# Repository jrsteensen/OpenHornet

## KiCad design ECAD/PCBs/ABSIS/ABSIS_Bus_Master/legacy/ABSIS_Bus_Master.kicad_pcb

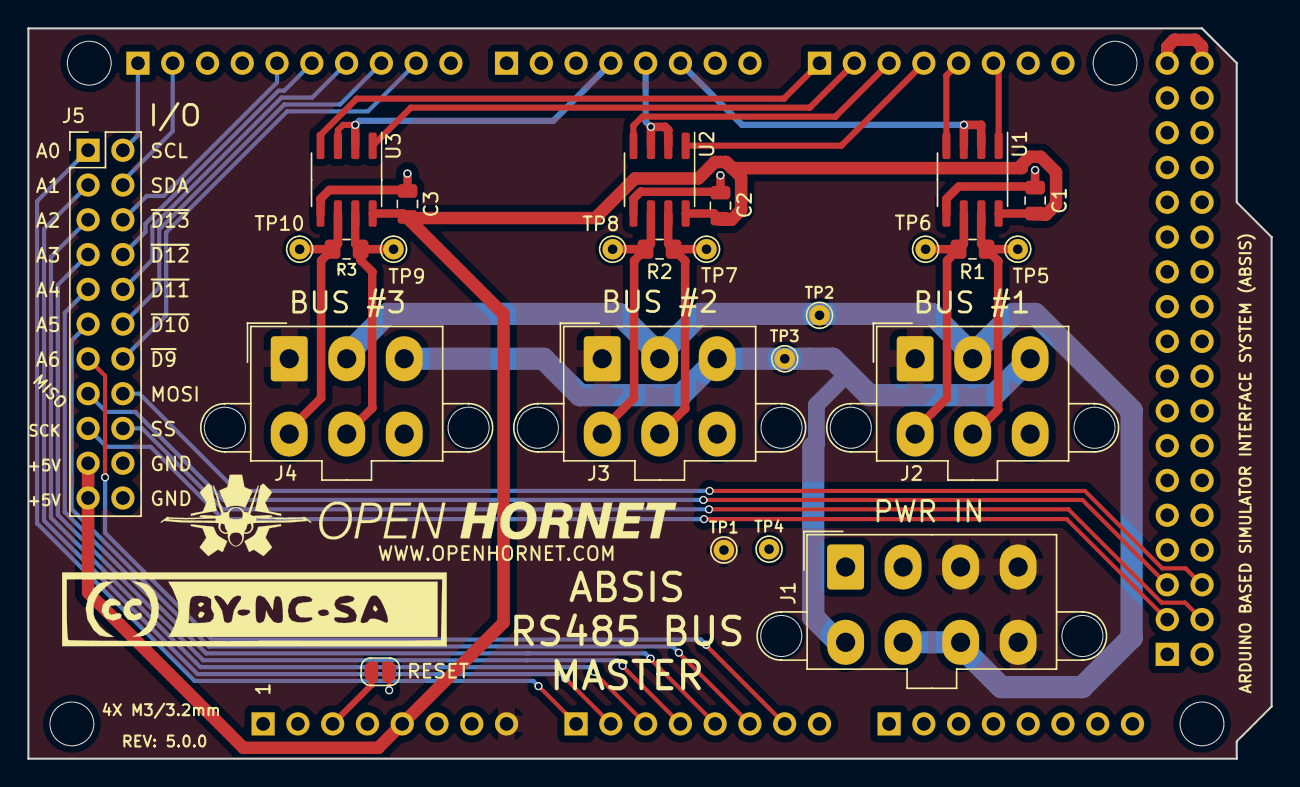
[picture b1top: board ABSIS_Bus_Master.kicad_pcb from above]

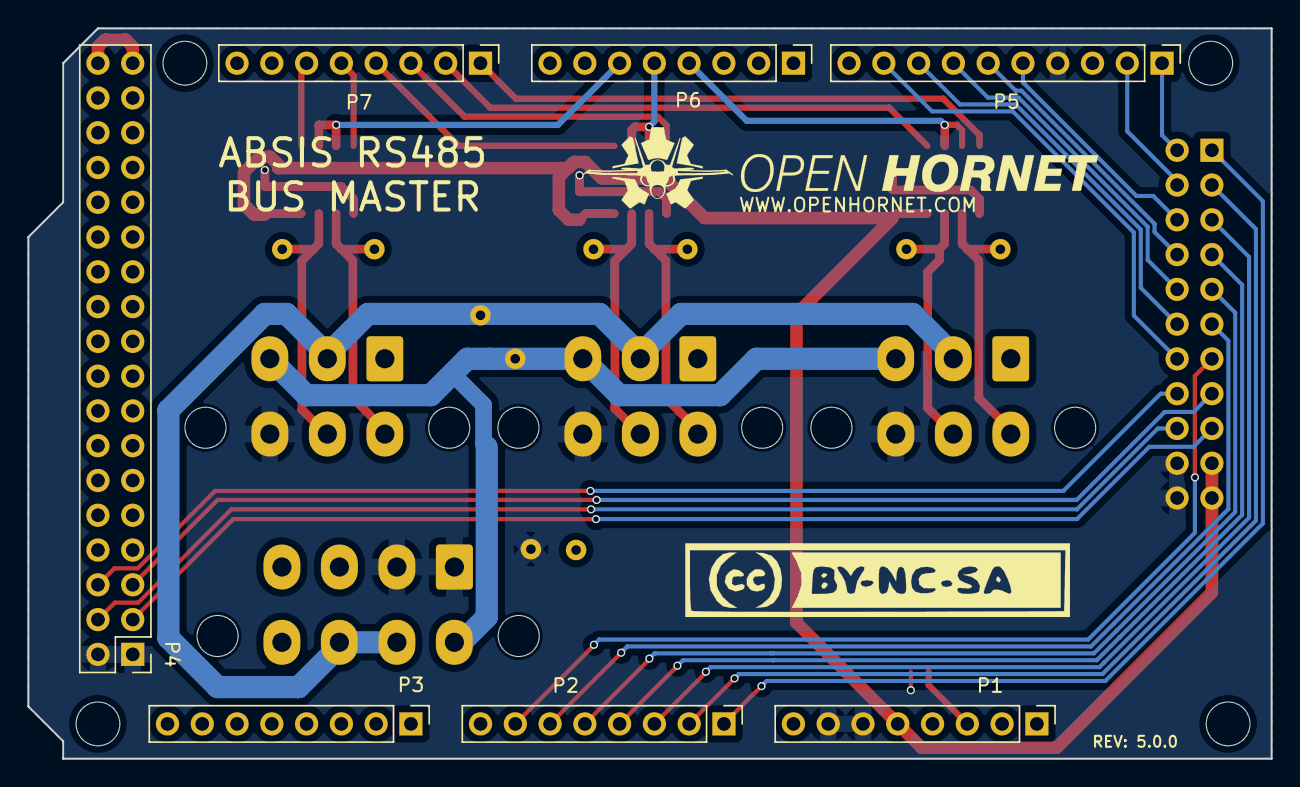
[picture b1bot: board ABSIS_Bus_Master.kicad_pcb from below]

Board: 2 copper layers, 90.8 x 53.3 mm, 40 parts (9 on the bottom side), 40 nets.

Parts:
C1, C2, C3: 0.1uF; C_0805_2012Metric
J1: Mini-Fit Jr. 2x04; Molex_Mini-Fit_Jr_5566-08A2_2x04_P4.20mm_Vertical
J2, J3, J4: Mini-Fit Jr. 2x03; Molex_Mini-Fit_Jr_5566-06A2_2x03_P4.20mm_Vertical
J5: PinHeader_2x11; PinHeader_2x11_P2.54mm_Vertical
LOGO1, LOGO4: LOGO; LOGO_CC-BY-NC-SA_Half_Large
LOGO2, LOGO3: LOGO; LOGO_OH_Text_Small
MK1, MK3, MK4, MK6: MH; MountingHole_3.2mm_M3_DIN965
P1: Power; PinHeader_1x08_P2.54mm_Vertical
P2, P3: Analog; PinHeader_1x08_P2.54mm_Vertical
P4: Digital; PinHeader_2x18_P2.54mm_Vertical
P5: PWM; PinHeader_1x10_P2.54mm_Vertical
P6: PWM; PinHeader_1x08_P2.54mm_Vertical
P7: Communication; PinHeader_1x08_P2.54mm_Vertical
R1, R2, R3: 120; R_0805_2012Metric_Pad1.15x1.40mm_HandSolder
RST1: RST; SolderJumper-2_P1.3mm_Open_RoundedPad1.0x1.5mm
TP1: TP-12; TestPoint_THTPad_D1.5mm_Drill0.7mm
TP2: TP-5V; TestPoint_THTPad_D1.5mm_Drill0.7mm
TP3: TP-3.3V; TestPoint_THTPad_D1.5mm_Drill0.7mm
TP4: TP-GND; TestPoint_THTPad_D1.5mm_Drill0.7mm
TP5: TP-B1B; TestPoint_THTPad_D1.5mm_Drill0.7mm
TP6: TP-B1A; TestPoint_THTPad_D1.5mm_Drill0.7mm
TP7: TP-B2B; TestPoint_THTPad_D1.5mm_Drill0.7mm
TP8: TP-B2A; TestPoint_THTPad_D1.5mm_Drill0.7mm
TP9: TP-B3B; TestPoint_THTPad_D1.5mm_Drill0.7mm
TP10: TP-B3A; TestPoint_THTPad_D1.5mm_Drill0.7mm
U1, U2, U3: MAX487EESA+T; SOIC-8_3.9x4.9mm_P1.27mm

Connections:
+5V: C1.1, C2.1, C3.1, J5.19, J5.21, P1.5, U1.8 (VCC), U2.8 (VCC), U3.8 (VCC)
+5VD: P4.35, P4.36
/2(**): P6.6, U1.2 (~RE), U1.3 (DE)
/3(**): P6.5, U2.2 (~RE), U2.3 (DE)
/4(**): P6.4, U3.2 (~RE), U3.3 (DE)
/9(**): J5.14, P5.9
/10(**): J5.12, P5.8
/11(**): J5.10, P5.7
/12(**): J5.8, P5.6
/13(**): J5.6, P5.5
/14(Tx3): P7.1, U3.4 (DI)
/15(Rx3): P7.2, U3.1 (RO)
/16(Tx2): P7.3, U2.4 (DI)
/17(Rx2): P7.4, U2.1 (RO)
/18(Tx1): P7.5, U1.4 (DI)
/19(Rx1): P7.6, U1.1 (RO)
/50(MISO): J5.15, P4.5
/51(MOSI): J5.16, P4.6
/52(SCK): J5.17, P4.3
/53(SS): J5.18, P4.4
/+3.3V_SUPPLY: J1.5, J2.3, J3.3, J4.3, TP3.1
/+5V_SUPPLY: J1.6, J1.7, J2.2, J3.2, J4.2, TP2.1
/+12V_SUPPLY: J1.3, J1.4, J1.8, J2.1, J3.1, J4.1, P1.8, TP1.1
/A0: J5.1, P2.1
/A1: J5.3, P2.2
/A2: J5.5, P2.3
/A3: J5.7, P2.4
/A4: J5.9, P2.5
/A5: J5.11, P2.6
/A6: J5.13, P2.7
/BUS1-A: J2.4, R1.2, TP6.1, U1.6 (A)
/BUS1-B: J2.5, R1.1, TP5.1, U1.7 (B)
/BUS2-A: J3.4, R2.2, TP8.1, U2.6 (A)
/BUS2-B: J3.5, R2.1, TP7.1, U2.7 (B)
/BUS3-A: J4.4, R3.2, TP10.1, U3.6 (A)
/BUS3-B: J4.5, R3.1, TP9.1, U3.7 (B)
/Reset: P1.3, RST1.2 (B)
/SCL: J5.2, P5.1
/SDA: J5.4, P5.2
GND: C1.2, C2.2, C3.2, J1.1, J1.2, J2.6, J3.6, J4.6, J5.20, J5.22, P1.6, P1.7, P4.1, P4.2, P5.4, RST1.1 (A), TP4.1, U1.5 (GND), U2.5 (GND), U3.5 (GND)

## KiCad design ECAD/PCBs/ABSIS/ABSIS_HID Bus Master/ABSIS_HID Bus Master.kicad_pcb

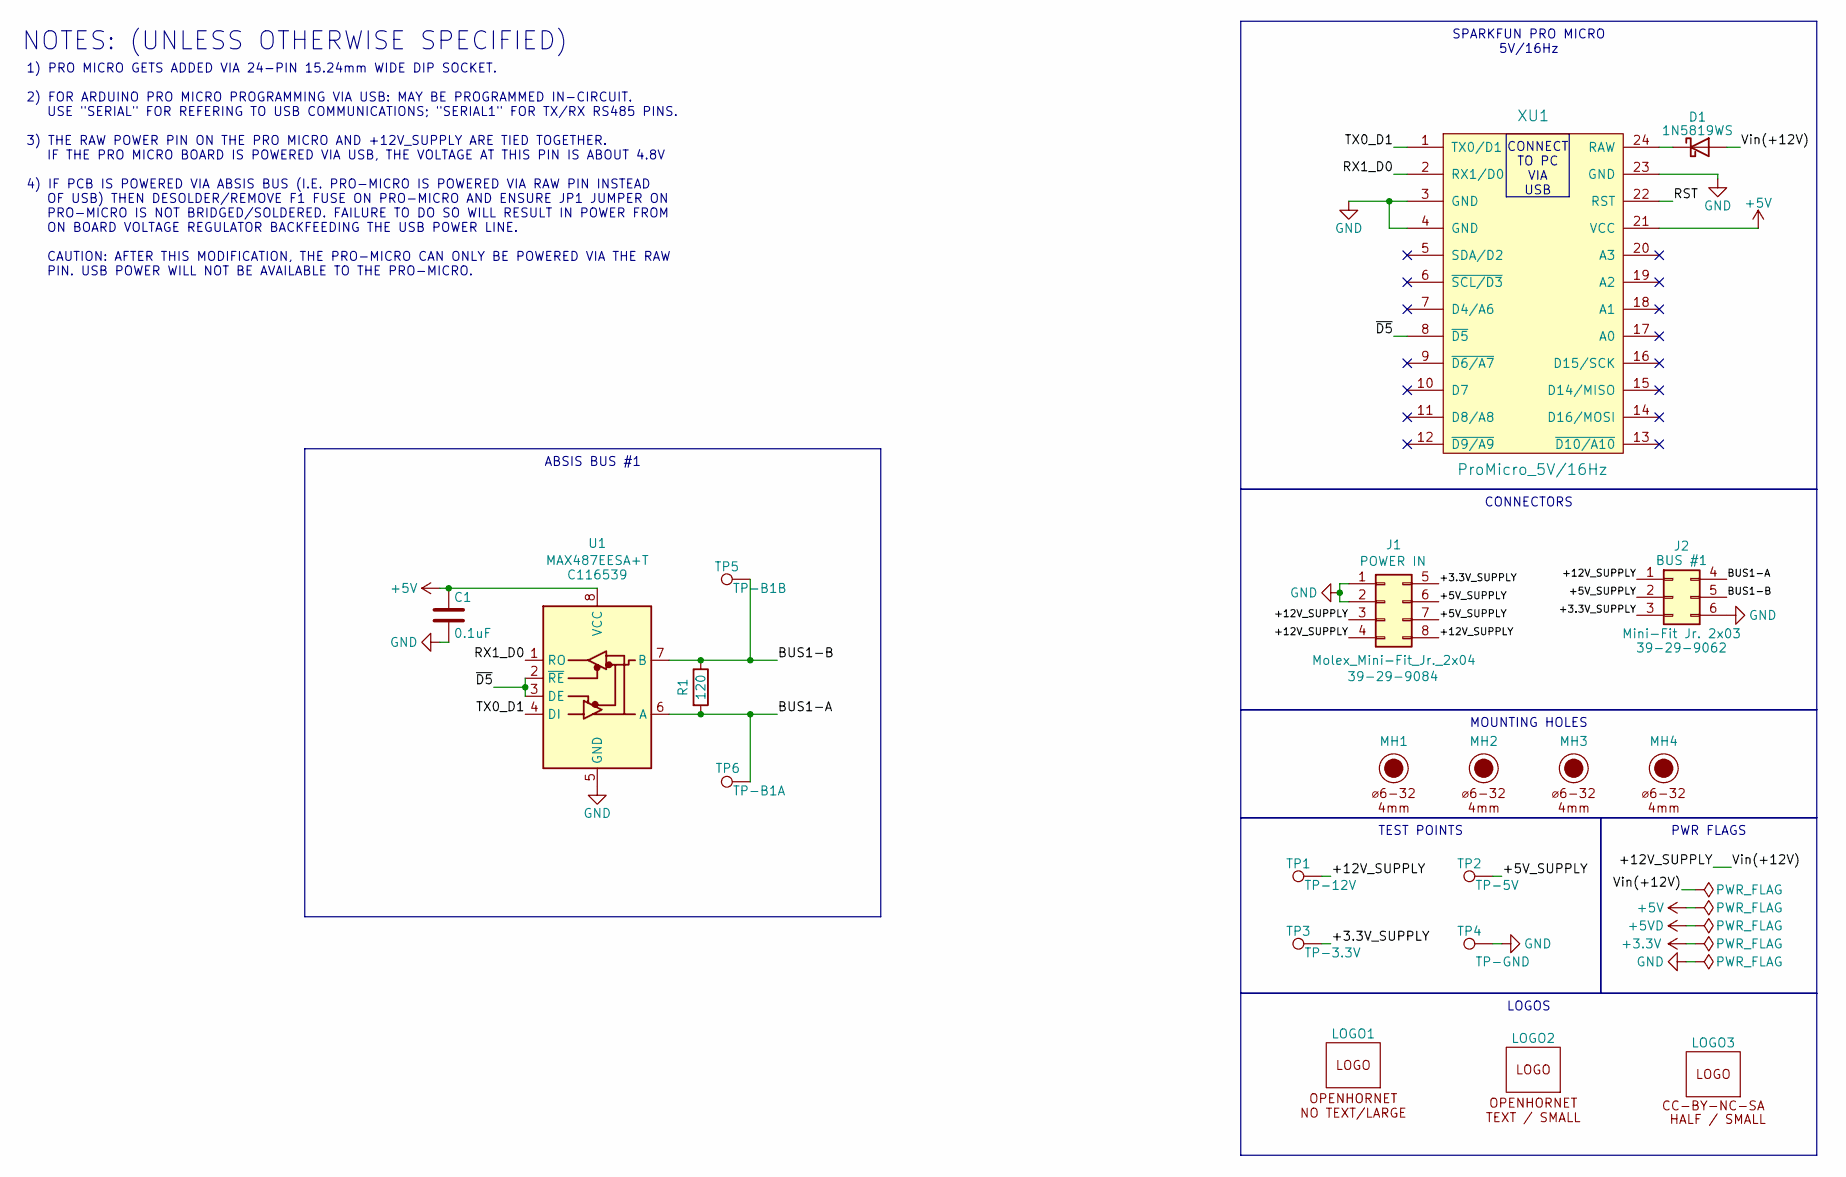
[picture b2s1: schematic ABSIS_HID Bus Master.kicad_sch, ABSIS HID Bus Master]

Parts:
C1: 0.1uF; C_0805_2012Metric; Manufacturer PN CC0805KRX7R9BB104; LCSC C49678
D1: 1N5819WS; D_SOD-323_HandSoldering; Manufacturer PN 1N5819WS; LCSC C191023
J1: Molex_Mini-Fit_Jr._2x04; Molex_Mini-Fit_Jr_5566-08A2_2x04_P4.20mm_Vertical; Manufacturer PN 39-29-9084; LCSC C587470
J2: Mini-Fit Jr. 2x03; Molex_Mini-Fit_Jr_5566-06A2_2x03_P4.20mm_Vertical; Manufacturer PN 39-29-9062; LCSC C505177
LOGO1: LOGO; LOGO_OH_NoText_Large
LOGO2: LOGO; LOGO_OH_Text_Small
LOGO3: LOGO; LOGO_CC-BY-NC-SA_Half_Small
MH1, MH2, MH3, MH4: 6x32 / 4mm; MountingHole_6-32_PHS
R1: 120; R_0805_2012Metric_Pad1.15x1.40mm_HandSolder; Manufacturer PN 0805W8F1200T5E; LCSC C17437
TP1, TP2, TP3, TP4, TP5, TP6: TestPoint; TestPoint_THTPad_D1.5mm_Drill0.7mm
U1: MAX487EESA+T; SOIC-8_3.9x4.9mm_P1.27mm; Manufacturer PN MAX487EESA+T; LCSC C116539
XU1: ProMicro_5V/16Hz; DIP-24_W15.24mm_Socket; Manufacturer PN Pro Micro - 5V/16MHz

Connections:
+5V: C1.1, U1.8 (VCC); also elsewhere on the board
/+3.3V_SUPPLY: J1.5, J2.3, TP3.1
/+5V_SUPPLY: J1.6, J1.7, J2.2, TP2.1
/+12V_SUPPLY: D1.2 (A), J1.3, J1.4, J1.8, J2.1, TP1.1
/BUS1-A: J2.4, R1.1, TP6.1, U1.6 (A)
/BUS1-B: J2.5, R1.2, TP5.1, U1.7 (B)
/RX1_D0: U1.1 (RO); also elsewhere on the board
/TX0_D1: U1.4 (DI); also elsewhere on the board
/~D5: U1.2 (~RE), U1.3 (DE); also elsewhere on the board
GND: C1.2, J1.1, J1.2, J2.6, TP4.1, U1.5 (GND); also elsewhere on the board
unnamed 11: D1.1 (K); also elsewhere on the board

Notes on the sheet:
CONNECTORS
SPARKFUN PRO MICRO 5V/16Hz
MOUNTING HOLES
PWR FLAGS
LOGOS
TEST POINTS
ABSIS BUS #1
CONNECT TO PC VIA USB
NOTES: (UNLESS OTHERWISE SPECIFIED)
1) PRO MICRO GETS ADDED VIA 24-PIN 15.24mm WIDE DIP SOCKET. 2) FOR ARDUINO PRO MICRO PROGRAMMING VIA USB: MAY BE PROGRAMMED IN-CIRCUIT. USE "SERIAL" FOR REFERING TO USB COMMUNICATIONS; "SERIAL1" FOR TX/RX RS485 PINS. 3) THE RAW POWER PIN ON THE PRO MICRO AND +12V_SUPPLY ARE TIED TOGETHER. IF THE PR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

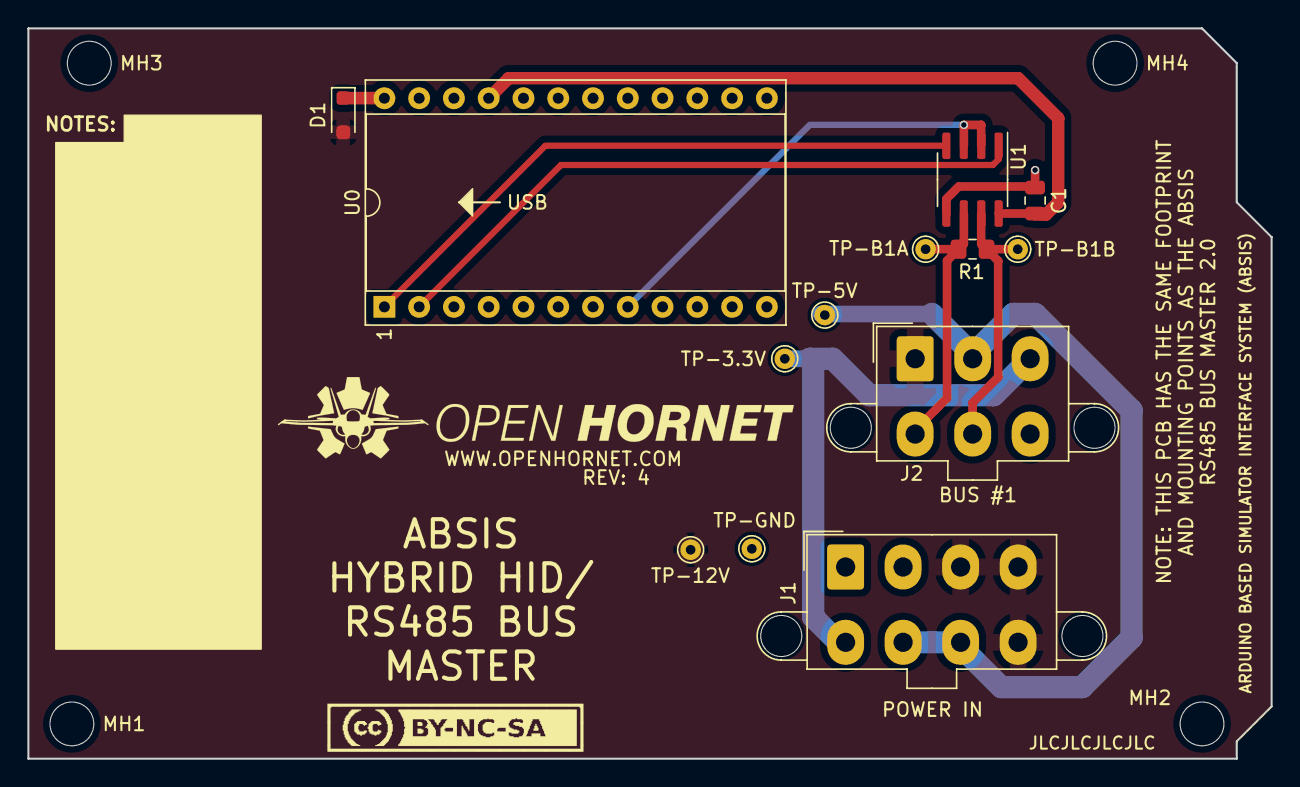
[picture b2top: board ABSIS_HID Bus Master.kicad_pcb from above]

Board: 2 copper layers, 90.8 x 53.3 mm, 20 parts (1 on the bottom side), 11 nets.

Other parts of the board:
U0: ProMicro_5V/16Hz; DIP-24_W15.24mm_Socket

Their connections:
+5V: U0.21 (VCC); also elsewhere on the board
/RX1_D0: U0.2 (RX1/D0); also elsewhere on the board
/TX0_D1: U0.1 (TX0/D1); also elsewhere on the board
/~D5: U0.8 (~D5); also elsewhere on the board
GND: U0.3 (GND), U0.4 (GND), U0.23 (GND); also elsewhere on the board
unnamed 11: U0.24 (RAW); also elsewhere on the board

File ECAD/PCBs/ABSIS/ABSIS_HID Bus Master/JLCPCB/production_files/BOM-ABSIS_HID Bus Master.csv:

Comment,Designator,Footprint,LCSC
MAX487EESA+T,U1,SOIC-8_3.9x4.9mm_P1.27mm,C116539
120,R1,R_0805_2012Metric_Pad1.15x1.40mm_HandSolder,C17437
0.1uF,C1,C_0805_2012Metric,C49678
Mini-Fit Jr. 2x03,J2,Molex_Mini-Fit_Jr_5566-06A2_2x03_P4.20mm_Vertical,C505177
Molex_Mini-Fit_Jr._2x04,J1,Molex_Mini-Fit_Jr_5566-08A2_2x04_P4.20mm_Vertical,C587470
ProMicro_5V/16Hz,U0,DIP-24_W15.24mm_Socket,

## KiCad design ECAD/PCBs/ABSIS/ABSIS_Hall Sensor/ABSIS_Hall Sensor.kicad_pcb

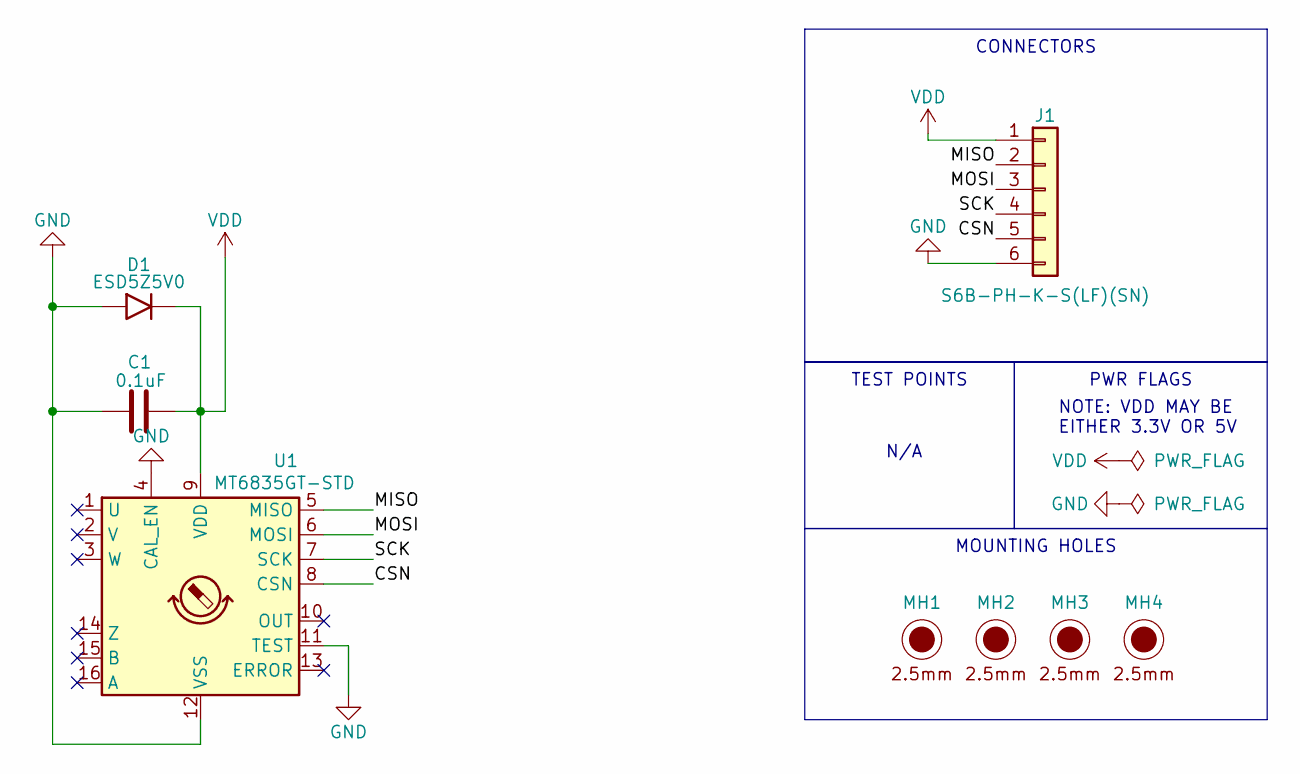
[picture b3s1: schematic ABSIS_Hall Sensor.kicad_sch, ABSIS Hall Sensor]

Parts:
C1: 0.1uF; C_0603_1608Metric; Manufacturer PN CC0603KRX7R9BB104; LCSC C14663
D1: ESD5Z5V0; D_SOD-523; Manufacturer PN ESD5Z5V0; LCSC C248788
J1: JST_PH_01x06; JST_PH_S6B-PH-K_1x06_P2.00mm_Horizontal; Manufacturer PN S6B-PH-K-S(LF)(SN); LCSC C265105
MH1, MH2, MH3, MH4: 2.5mm; MountingHole_2.5mm
U1: MT6835GT-STD; TSSOP-16_4.4x5mm_P0.65mm; Manufacturer PN MT6835GT-STD; LCSC C2932578

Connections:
/CSN: J1.5, U1.8 (CSN)
/MISO: J1.2, U1.5 (MISO)
/MOSI: J1.3, U1.6 (MOSI)
/SCK: J1.4, U1.7 (SCK)
GND: C1.2, D1.2 (A2), J1.6, U1.4 (CAL_EN), U1.11 (TEST), U1.12 (VSS)
VDD: C1.1, D1.1 (A1), J1.1, U1.9 (VDD)

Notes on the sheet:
MOUNTING HOLES
PWR FLAGS
CONNECTORS
TEST POINTS
N/A
NOTE: VDD MAY BE EITHER 3.3V OR 5V

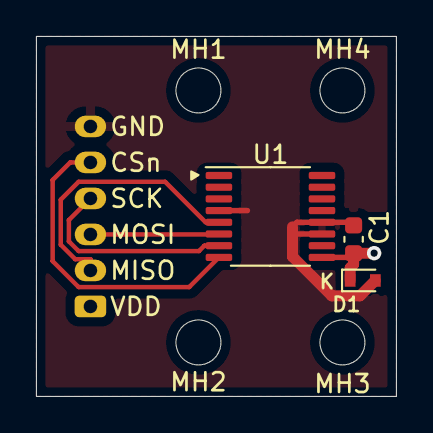
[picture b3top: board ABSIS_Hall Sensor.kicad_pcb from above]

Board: 2 copper layers, 20.0 x 20.0 mm, 8 parts (1 on the bottom side), 6 nets.

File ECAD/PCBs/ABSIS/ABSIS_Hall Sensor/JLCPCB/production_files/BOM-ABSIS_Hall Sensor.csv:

Comment,Designator,Footprint,LCSC
0.1uF,C1,C_0603_1608Metric,C14663
ESD5Z5V0,D1,D_SOD-523,C248788
JST_PH_01x06,J1,JST_PH_S6B-PH-K_1x06_P2.00mm_Horizontal,C265105
MT6835GT,U1,TSSOP-16_4.4x5mm_P0.65mm,C2932578

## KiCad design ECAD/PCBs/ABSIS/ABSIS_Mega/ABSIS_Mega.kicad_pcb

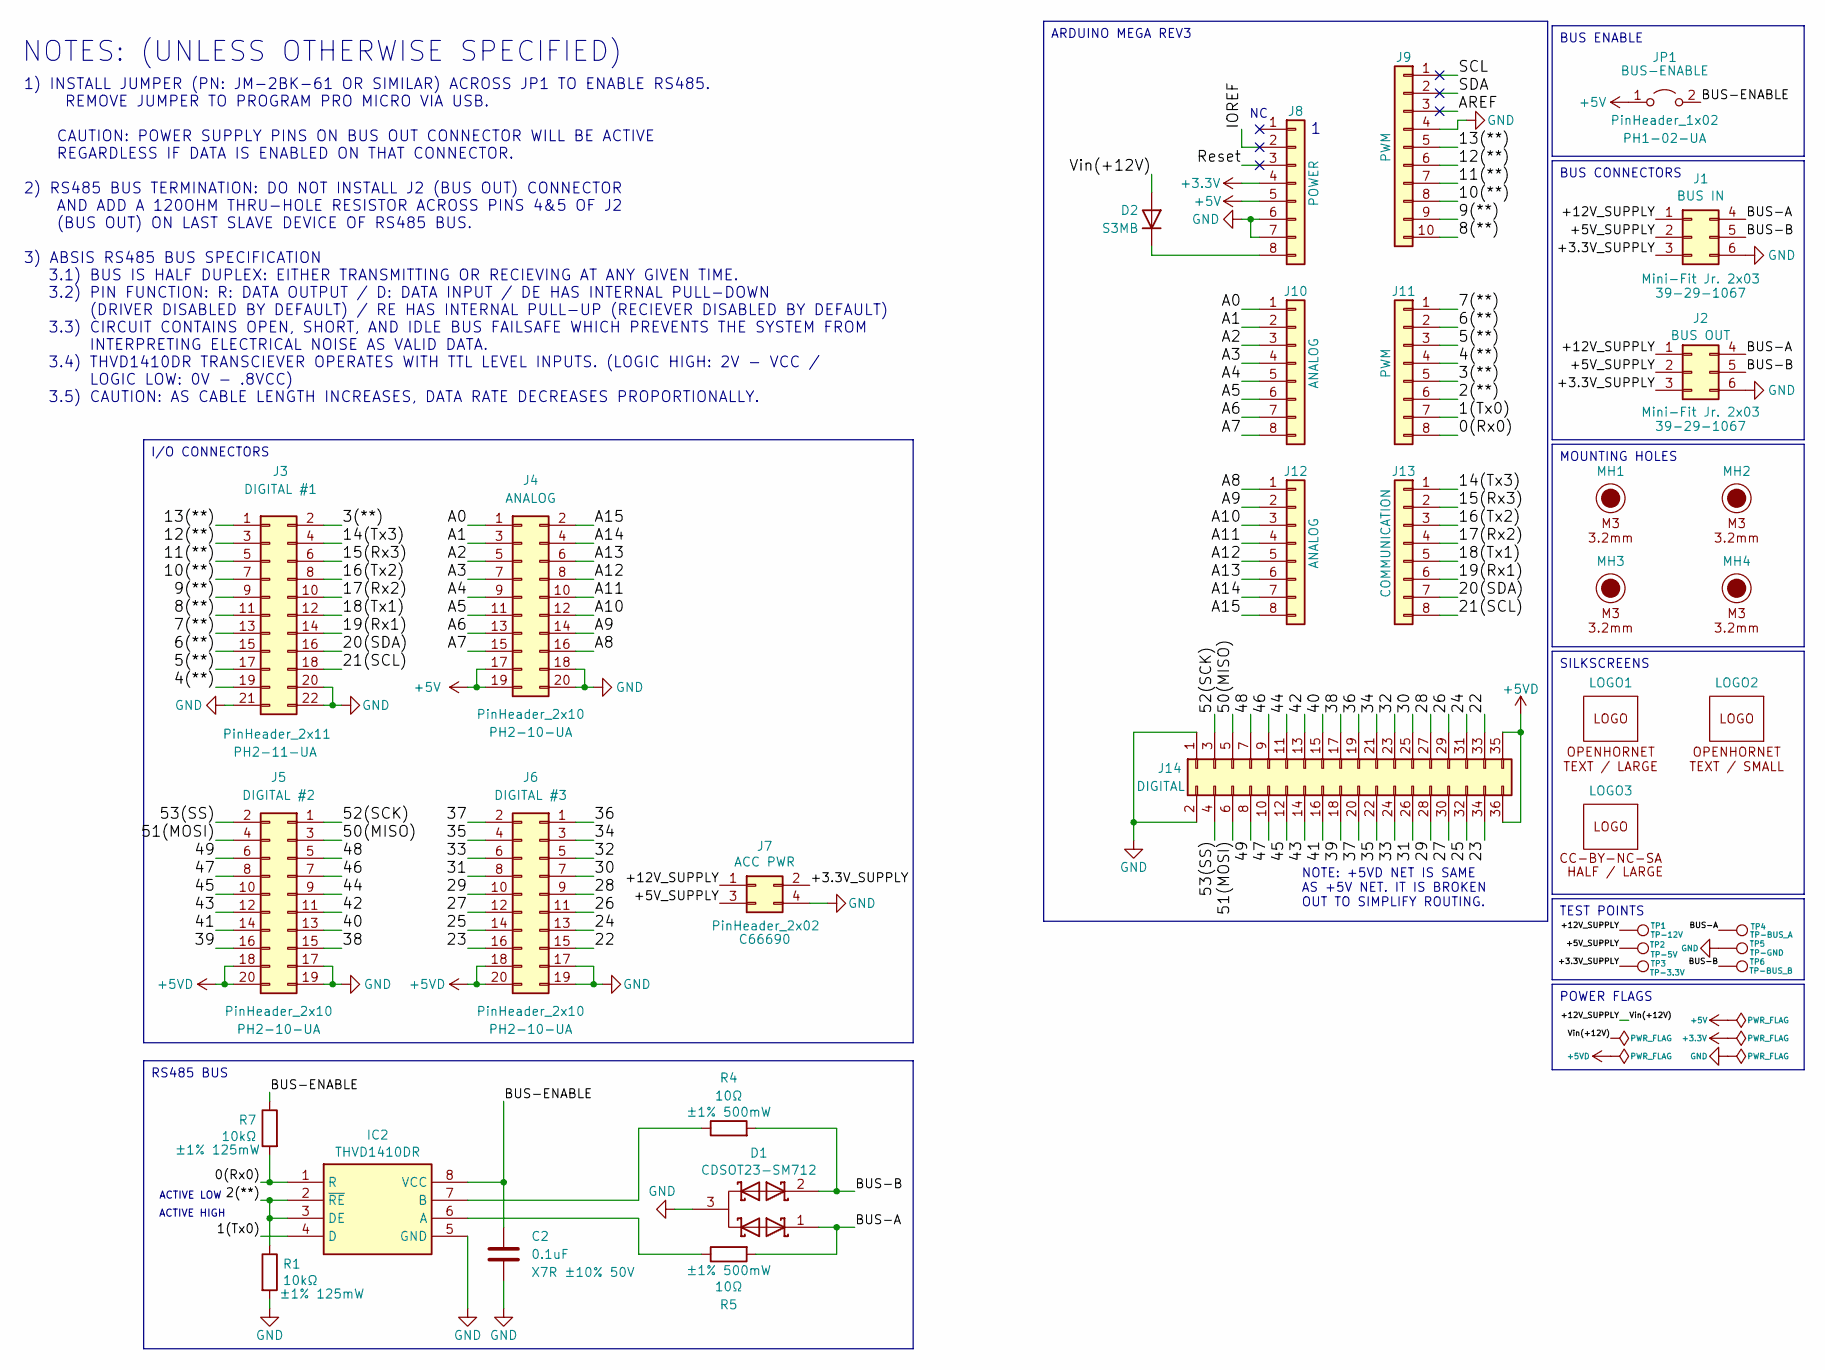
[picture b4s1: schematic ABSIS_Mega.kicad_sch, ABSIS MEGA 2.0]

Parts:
C2: 0.1uF; C_0805_2012Metric; Manufacturer PN CC0805KRX7R9BB104; LCSC C49678
D1: CDSOT23-SM712; Manufacturer PN CDSOT23-SM712; LCSC C404012
D2: S3MB; D_SMB; Manufacturer PN S3MB; LCSC C47524
IC2: THVD1410DR; Manufacturer PN THVD1410DR; LCSC C2671345
J1, J2: Mini-Fit Jr. 2x03; Molex_Mini-Fit_Jr_5569-06A1_2x03_P4.20mm_Horizontal; Manufacturer PN 39-29-1067; LCSC C589019
J3: PinHeader_2x11; PinHeader_2x11_P2.54mm_Vertical; Manufacturer PN PH2-11-UA
J4, J5, J6: PinHeader_2x10; PinHeader_2x10_P2.54mm_Vertical; Manufacturer PN PH2-10-UA
J7: PinHeader_2x02; PinHeader_2x02_P2.54mm_Vertical; Manufacturer PN C66690; LCSC C66690
J8, J10, J11, J12, J13: PinHeader_1x08; PinHeader_1x08_P2.54mm_Vertical; Manufacturer PN PH1-08-UA
J9: PinHeader_1x10; PinHeader_1x10_P2.54mm_Vertical; Manufacturer PN PH1-10-UA
J14: PinHeader_2x18; PinHeader_2x18_P2.54mm_Vertical; Manufacturer PN PH2-18-UA
JP1: PinHeader_1x02; PinHeader_1x02_P2.54mm_Vertical; Manufacturer PN PH1-02-UA
LOGO1: LOGO; LOGO_OH_Text_Large
LOGO2: LOGO; LOGO_OH_Text_Small
LOGO3: LOGO; LOGO_CC-BY-NC-SA_Half_Large
MH1, MH2, MH3, MH4: M3 / 3.2mm; MountingHole_3.2mm_M3_DIN965
R1, R7: 10kΩ; R_0805_2012Metric; Manufacturer PN AC0805FR-0710KL; LCSC C140868
R4, R5: 10Ω; R_0805_2012Metric; Manufacturer PN CRCW080510R0FKEAHP; LCSC C844598
TP1, TP2, TP3, TP4, TP5, TP6: TestPoint; TestPoint_THTPad_D1.5mm_Drill0.7mm

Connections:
+3.3V: J8.4
+5V: J4.17, J4.19, J8.5, JP1.1 (A)
+5VD: J5.18, J5.20, J6.18, J6.20, J14.35, J14.36
/0(Rx0): IC2.1 (R), J11.8, R7.2
/1(Tx0): IC2.4 (D), J11.7
/2(**): IC2.2 (~RE), IC2.3 (DE), J11.6, R1.1
/3(**): J3.2, J11.5
/4(**): J3.19, J11.4
/5(**): J3.17, J11.3
/6(**): J3.15, J11.2
/7(**): J3.13, J11.1
/8(**): J3.11, J9.10
/9(**): J3.9, J9.9
/10(**): J3.7, J9.8
/11(**): J3.5, J9.7
/12(**): J3.3, J9.6
/13(**): J3.1, J9.5
/14(Tx3): J3.4, J13.1
/15(Rx3): J3.6, J13.2
/16(Tx2): J3.8, J13.3
/17(Rx2): J3.10, J13.4
/18(Tx1): J3.12, J13.5
/19(Rx1): J3.14, J13.6
/20(SDA): J3.16, J13.7
/21(SCL): J3.18, J13.8
/22: J6.15, J14.33
/23: J6.16, J14.34
/24: J6.13, J14.31
/25: J6.14, J14.32
/26: J6.11, J14.29
/27: J6.12, J14.30
/28: J6.9, J14.27
/29: J6.10, J14.28
/30: J6.7, J14.25
/31: J6.8, J14.26
/32: J6.5, J14.23
/33: J6.6, J14.24
/34: J6.3, J14.21
/35: J6.4, J14.22
/36: J6.1, J14.19
/37: J6.2, J14.20
/38: J5.15, J14.17
/39: J5.16, J14.18
/40: J5.13, J14.15
/41: J5.14, J14.16
/42: J5.11, J14.13
/43: J5.12, J14.14
/44: J5.9, J14.11
/45: J5.10, J14.12
/46: J5.7, J14.9
/47: J5.8, J14.10
/48: J5.5, J14.7
/49: J5.6, J14.8
/50(MISO): J5.3, J14.5
/51(MOSI): J5.4, J14.6
/52(SCK): J5.1, J14.3
/53(SS): J5.2, J14.4
/+3.3V_SUPPLY: J1.3, J2.3, J7.2, TP3.1 (1_1)
/+5V_SUPPLY: J1.2, J2.2, J7.3, TP2.1 (1_1)
/+12V_SUPPLY: D2.2 (A), J1.1, J2.1, J7.1, TP1.1 (1_1)
/A0: J4.1, J10.1
/A1: J4.3, J10.2
/A2: J4.5, J10.3
/A3: J4.7, J10.4
/A4: J4.9, J10.5
/A5: J4.11, J10.6
/A6: J4.13, J10.7
/A7: J4.15, J10.8
/A8: J4.16, J12.1
/A9: J4.14, J12.2
/A10: J4.12, J12.3
/A11: J4.10, J12.4
/A12: J4.8, J12.5
/A13: J4.6, J12.6
/A14: J4.4, J12.7
/A15: J4.2, J12.8
/AREF: J9.3
/BUS-A: D1.1, J1.4, J2.4, R5.2, TP4.1 (1_1)
/BUS-B: D1.2, J1.5, J2.5, R4.2, TP6.1 (1_1)
/BUS-ENABLE: C2.2, IC2.8 (VCC), JP1.2 (B), R7.1
/IOREF: J8.2
/Reset: J8.3
/SCL: J9.1
/SDA: J9.2
GND: C2.1, D1.3, IC2.5 (GND), J1.6, J2.6, J3.20, J3.21, J3.22, J4.18, J4.20, J5.17, J5.19, J6.17, J6.19, J7.4, J8.6, J8.7, J9.4, J14.1, J14.2, R1.2, TP5.1 (1_1)
unnamed: D2.1 (K), J8.8
unnamed: IC2.6 (A), R5.1
unnamed: IC2.7 (B), R4.1

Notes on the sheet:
1) INSTALL JUMPER (PN: JM-2BK-61 OR SIMILAR) ACROSS JP1 TO ENABLE RS485. REMOVE JUMPER TO PROGRAM PRO MICRO VIA USB. CAUTION: POWER SUPPLY PINS ON BUS OUT CONNECTOR WILL BE ACTIVE REGARDLESS IF DATA IS ENABLED ON THAT CONNECTOR. 2) RS485 BUS TERMINATION: DO NOT INSTALL J2 (BUS OUT) CONNECTOR AND AD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
NOTES: (UNLESS OTHERWISE SPECIFIED)
ACTIVE HIGH
ACTIVE LOW
NOTE: +5VD NET IS SAME AS +5V NET. IT IS BROKEN OUT TO SIMPLIFY ROUTING.
SILKSCREENS
POWER FLAGS
RS485 BUS
ARDUINO MEGA REV3
BUS ENABLE
BUS CONNECTORS
TEST POINTS
MOUNTING HOLES
I/O CONNECTORS

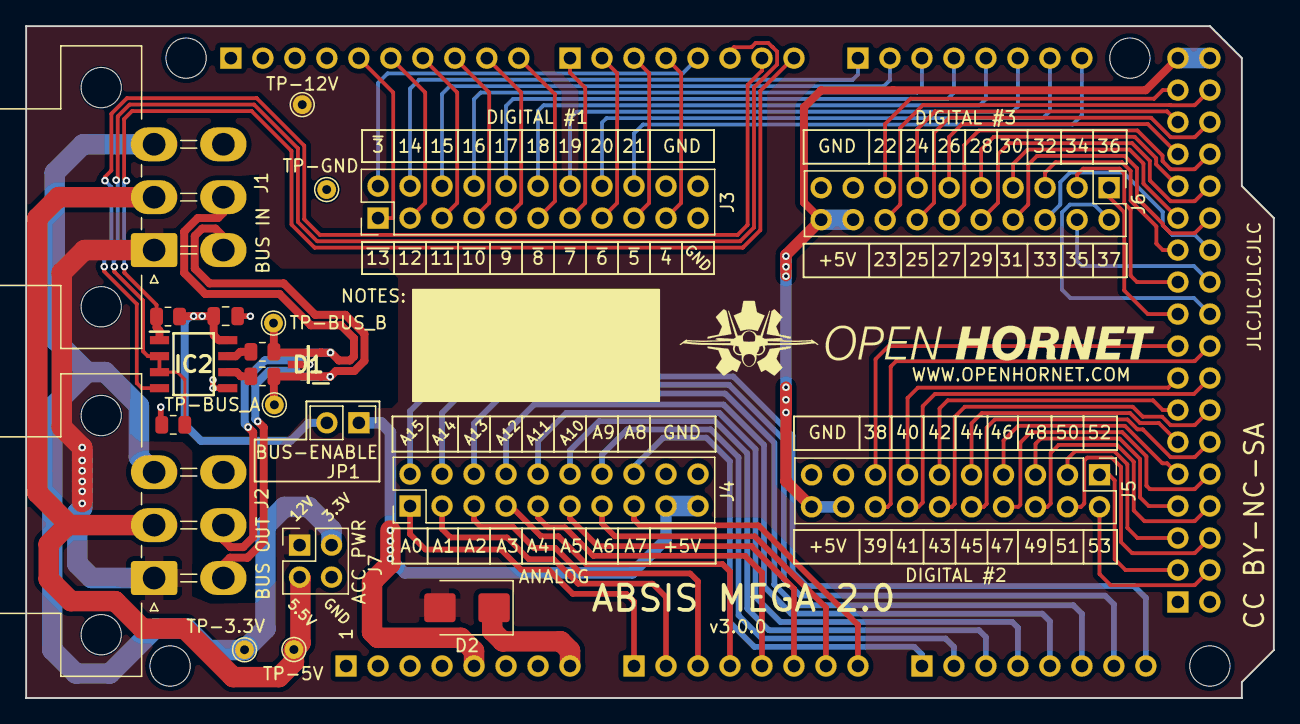
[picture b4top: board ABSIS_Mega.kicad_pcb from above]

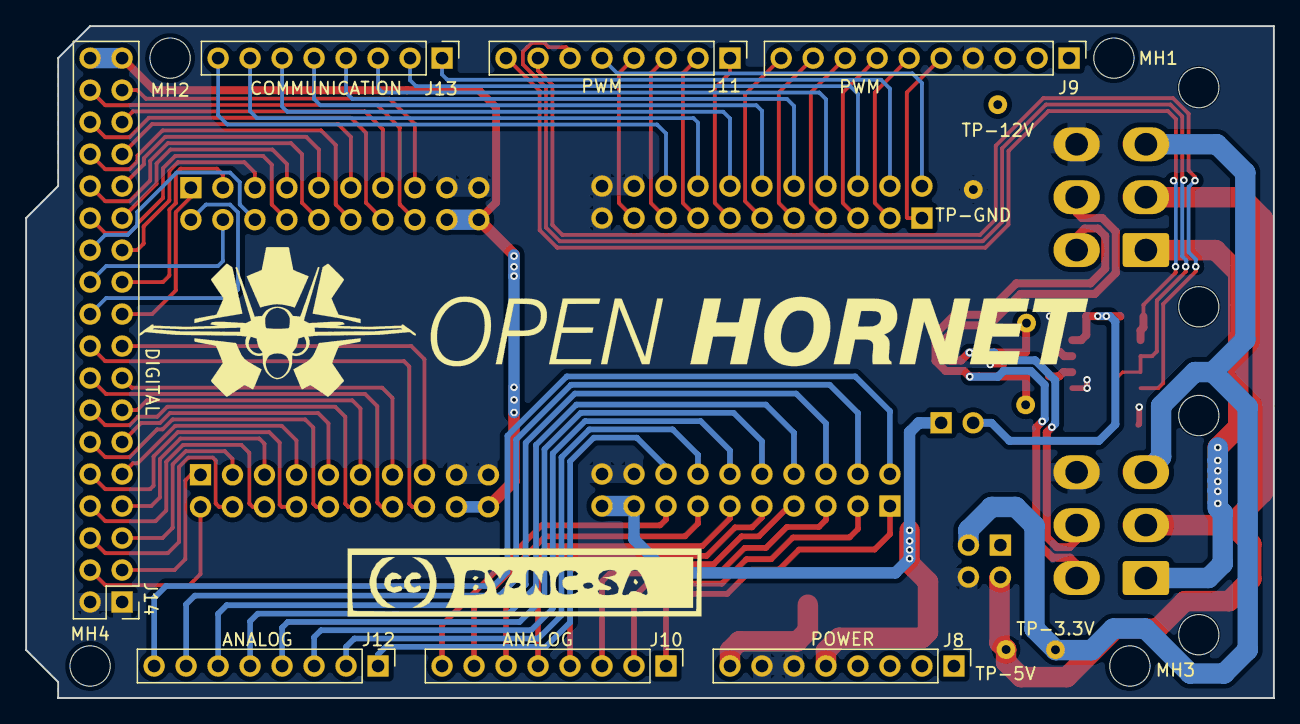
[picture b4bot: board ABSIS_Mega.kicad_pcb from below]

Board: 2 copper layers, 99.1 x 53.3 mm, 36 parts (13 on the bottom side), 82 nets.

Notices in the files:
ECAD/PCBs/ABSIS/ABSIS_HID Bus Master/ABSIS_HID Bus Master.kicad_pcb:
License:  CC BY-NC-SA
parts and their libraries:
https://creativecommons.org/licenses/by-nc-sa/4.0
